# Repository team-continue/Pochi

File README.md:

# Pochi
CoREストライダー部門用のロボット「Pochi」のメインレポジトリです。

機体の構成は [Pochi の構成解説 — メカ・電装・制御](ROBOT_OVERVIEW.md) を参照してください。

詳細はドキュメントサイトを参照してください。

## 開発ルール
開発はブランチを切って Pull Request で main にマージしてください。main への直接コミットは禁止です。
ブランチ名: 機能追加は feature/hogehoge、バグ修正は fix/hogehoge
パッケージ名: pochi_hoge（タブ補完で一覧表示できるように）
Formatting (CI)
Push 時に CI が ament_clang_format を実行し、必要ならブランチへ自動コミットします。 main ブランチには自動 push しません。

## ビルド
``` shell
cd ~/ros2_ws
source /opt/ros/humble/setup.bash
rosdep install --from-paths src -i -y
colcon build --symlink-install
source install/setup.bash
```

## 起動方法
```
# シミュレータモード（デフォルト: /sim_odom使用）
ros2 launch core_launch navigation.launch.py

# シミュレータ + FAST-LIOオドメトリ
ros2 launch core_launch navigation.launch.py odom_source:=fastlio

# 実機モード（FAST-LIO + body_controller、TCP endpoint無し）
ros2 launch core_launch navigation.launch.py environment:=real

# 実機モード（GUI・ショートカットから）
# .bashrc が非対話シェルで早期 return するため、このラッパーを使用
ros2 run core_launch navigation.sh

# ボディコントローラ単体
ros2 launch core_launch navigation.launch.py environment:=real map_name:=curious_house.png

# 実機ハードウェア
ros2 launch core_hardware core_hardware.launch.py
```
Launch 引数の詳細はドキュメントサイトの「クイックスタート」を参照してください。

## 2026-10-14 の変更整理

作業版は `work/pochi-consolidation-20261014` に、CAD、起立・低速歩行、MPC・横ジャンプ、
LP-ACRLの過去実験、トルク余裕学習、歩行・停止の再学習を分けてコミットしています。
変更の記録は `pochi_rl/repository_state_20261014.json` を参照してください。

実際にSSH先で学習したソースとアセットは `archive/v19-ssh-20261014`、
Orinの実機コード・配布モデルは `archive/orin-hardware-20261014` に保存しています。
前者の作業ツリーは `.training-worktrees/v19-ssh-20261014/`、後者は
`.hardware-worktrees/orin-20261014/` です。SSH側の学習時のアセットと、この作業版の
CADアセットは異なるため、履歴を分けてそのまま残しています。

次の学習は利用許可が戻ったローカルGPUを使用します。大きい学習チェックポイント・
動画・CSVは各ホストの元の保存先に残し、実機起動に必要な小さいTorchScriptモデルと
契約は実機ブランチに含めています。機体固有のキャリブレーションはOrin上で保持します。
今回の整理は学習開始、実機の制御コード変更、サービス再起動を伴いません。

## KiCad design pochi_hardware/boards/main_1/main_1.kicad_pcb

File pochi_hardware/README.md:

# Pochi Hardware

Pochiの回路、STM32/Teensyファームウェア、ホスト側通信ツール、Python API、
Web joint viewerをまとめています。

## Python APIとWeb joint viewer

`pochi_client`はTeensy USB/UDP bridgeと通信するPython APIです。12台分のMIT指令を
1 packetで送信し、12台の状態とIMUを1 packetで受信します。Web viewerは左側の
3Dモデルへ現在姿勢を反映し、右側から関節の選択・目標角度・全体Torque ON/OFFを
操作できます。

### セットアップ

```bash
cd ~/Documents/GitHub/Pochi
uv sync

cd pochi_hardware/web
npm install
```

### Web joint viewer

3つのターミナルを使います。

#### 1. USB/UDP bridge

macOSではTeensyのdevice名を確認して起動します。

```bash
cd ~/Documents/GitHub/Pochi
uv run python pochi_hardware/src/teensy_udp_bridge.py \
  --serial /dev/cu.usbmodem176277501 \
  --command-bind 127.0.0.1:15000 \
  --state-dest 127.0.0.1:15001
```

#### 2. UDP/WebSocket server

```bash
cd ~/Documents/GitHub/Pochi
uv run python -m pochi_hardware.web.server
```

状態確認用URLは`http://127.0.0.1:8765/health`、WebSocketは
`ws://127.0.0.1:8765/ws`です。

#### 3. Web UI

```bash
cd ~/Documents/GitHub/Pochi/pochi_hardware/web
npm run dev
```

ブラウザで`http://127.0.0.1:3000`を開きます。

### Viewer controls and safety

- 左の3Dモデルは12軸の実角度を常時反映します。ドラッグで視点回転、スクロールでズーム、関節をクリックすると選択できます。
- 右の関節一覧または3Dモデルから1軸を選び、スライダーでMIT controlの目標角を更新します。
- `TORQUE ON`は全12台の現在角を初期目標に設定してから全軸をEnableします。
- 全12台から有効なCAN feedbackが返り、Faultがないときだけ`TORQUE ON`できます。
- 最後のWeb画面を閉じた場合、WebSocket serverは全軸を自動Disableします。
- WebSocket server終了時は全軸Disableとemergency-stop packetを送ります。
- Hip/Thigh/Calfの暫定UI制限はそれぞれ±55°、±150°、-165〜25°です。機構限界確定後にWeb UIとserverの両方を更新してください。

### Client API

```python
from pochi_client import PochiClient

with PochiClient() as robot:
    state = robot.wait_for_state(timeout=1.0)
    robot.set_mit(
        "front_left_hip",
        position_rad=0.2,
        velocity_rad_s=0.0,
        kp=20.0,
        kd=0.5,
        torque_nm=0.0,
        enable=True,
    )
    robot.disable_all()
```

### Joint layout

脚とCAN IDの対応です。各脚では足先側からIDが増えます。

| Leg | Hip | Thigh | Calf |
| --- | ---: | ---: | ---: |
| Front left | 2 | 1 | 0 |
| Rear left | 5 | 4 | 3 |
| Rear right | 8 | 7 | 6 |
| Front right | 11 | 10 | 9 |

Web画面には誤認防止のためCAN IDを常時表示します。

### テストとWebビルド

```bash
cd ~/Documents/GitHub/Pochi
uv run pytest -q

cd pochi_hardware/web
npm run build
```

## Jetson Orin NanoのSPI0ピン設定

`systemd/pochi-spi0-pinmux.service`は、Jetson Orin Nanoの40ピンヘッダーにある
SPI0をPochi用に設定します。

使用する物理ピンは次の4本です。

| 物理ピン | 信号 |
| --- | --- |
| 19 | SPI0 MOSI |
| 21 | SPI0 MISO |
| 23 | SPI0 SCK |
| 24 | SPI0 CS0 |

### インストールと有効化

以下は、この`pochi_hardware`ディレクトリで実行します。

```bash
sudo install -o root -g root -m 0644 \
  systemd/pochi-spi0-pinmux.service \
  /etc/systemd/system/pochi-spi0-pinmux.service

sudo systemctl daemon-reload
sudo systemctl enable --now pochi-spi0-pinmux.service
sudo systemctl restart pochi-spi0-pinmux.service
```

状態を確認します。

```bash
systemctl is-enabled pochi-spi0-pinmux.service
systemctl is-active pochi-spi0-pinmux.service
```

それぞれ`enabled`と`active`になれば設定完了です。

### STM32との通信確認

STM32へSPIエコーファームウェアを書き込んだ状態で、Orinから20 MHzのテストを
実行します。

```bash
cd ~/pochi
./orin_spi_test /dev/spidev0.0 20000000
```

成功時は次のように表示されます。

```text
TX=DE AD BE E1  ECHO=DE AD BE E1
PASS: STM32 echoed the Orin request
```

### 停止とGPIO設定の復元

サービスを停止すると`ExecStop`が実行され、SPIパッドを開発用Orinで取得した
元のGPIO設定へ戻します。

```bash
sudo systemctl disable --now pochi-spi0-pinmux.service
```

サービス自体も削除する場合は、停止後に次を実行します。

```bash
sudo rm -f /etc/systemd/system/pochi-spi0-pinmux.service
sudo systemctl daemon-reload
```

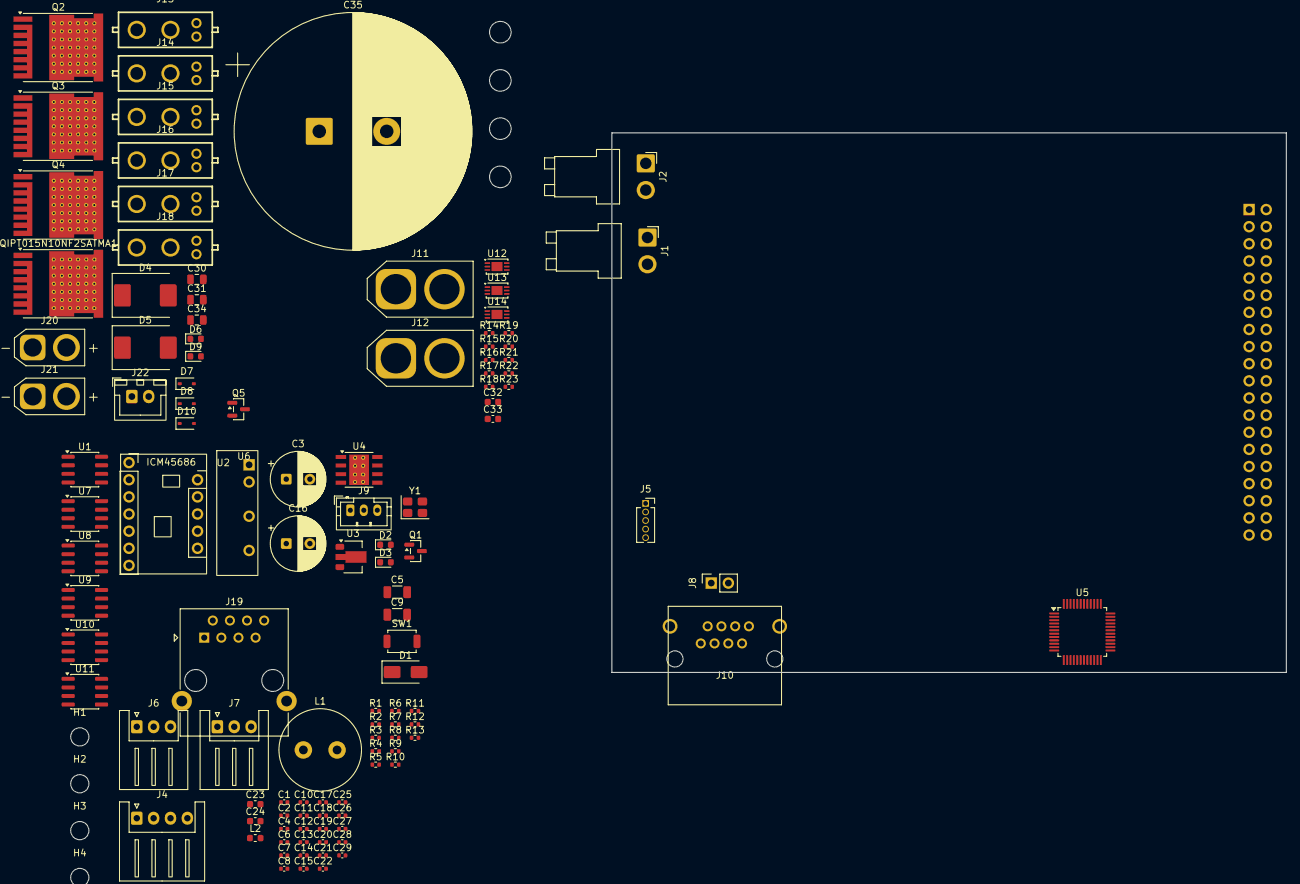
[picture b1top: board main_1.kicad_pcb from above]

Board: 2 copper layers, 100.0 x 80.0 mm, 122 parts (1 on the bottom side), 83 nets, no tracks yet.

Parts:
C1, C19, C20, C21, C22, C25, C26, C27, C28: 100n; C_0402_1005Metric
C2: 4.7u/16V; C_0402_1005Metric
C3, C16: 220u; CP_Radial_D8.0mm_P3.50mm
C4: 10u/0603/25V; C_0402_1005Metric
C5, C9: 4.7u; C_1206_3216Metric
C6, C7, C10, C13, C15: 100n/16V; C_0402_1005Metric
C8, C11: 10p/50V; C_0402_1005Metric
C12: 10u/0402/6.3V; C_0402_1005Metric
C14: 0.01u; C_0402_1005Metric
C17: 10n/50V; C_0402_1005Metric
C18: 1u/25V; C_0402_1005Metric
C23: 2.2u; C_0603_1608Metric
C24: 1u; C_0603_1608Metric
C29: 0.1u; C_0402_1005Metric
C30, C31, C34: 1.5u; C_0805_2012Metric
C32, C33: 10n; C_0603_1608Metric
C35: 10000u/50V; CP_Radial_D35.0mm_P10.00mm_SnapIn
D1: SS34; D_SMA
D2, D6: Green; LED_0603_1608Metric
D3: Yello; LED_0603_1608Metric
D4, D5: SMDJ48A; D_SMC
D7, D8, D10: IPT015N10NF2SATMA1; D_SOD-323
D9: RED; LED_0603_1608Metric
H1, H2, H3, H4: MountingHole; MountingHole_2.7mm_M2.5
H5, H6, H7, H8: MountingHole; MountingHole_3.2mm_M3_DIN965
J1, J2: VH; JST_VH_B2PS-VH_1x02_P3.96mm_Horizontal
J3: Conn_02x20_Odd_Even; PinSocket_2x20_P2.54mm_Vertical
J4: RS485; JST_XH_S4B-XH-A_1x04_P2.50mm_Horizontal
J5: Pad; PinSocket_1x05_P1.27mm_Vertical
J6, J7: XH; JST_XH_S3B-XH-A_1x03_P2.50mm_Horizontal
J8: DIP; PinSocket_1x02_P2.54mm_Vertical
J9: PH; JST_PH_B3B-PH-K_1x03_P2.00mm_Vertical
J10: RJ45; 7810-8P8C
J11, J12: XT60-M; AMASS_XT60-M_1x02_P7.20mm_Vertical
J13, J14, J15, J16, J17, J18: XT30(2+2)-M; CONN-TH_XT30PB-M
J19: RJ45; RJ45_Ninigi_GE
J20, J21: XT30; AMASS_XT30U-F_1x02_P5.0mm_Vertical
J22: XH; JST_XH_B2B-XH-A_1x02_P2.50mm_Vertical
L1: 22u; L_Radial_D12.0mm_P5.00mm_Fastron_11P
L2: 600Ω; L_0603_1608Metric
Q1: S9012; SOT-23
Q2, Q3, Q4: IPT015N10NF2SATMA1; Infineon_PG-HSOF-8-1_ThermalVias
Q5: 2N7002; SOT-23
QIPT015N10NF2SATMA1: NMOS; Infineon_PG-HSOF-8-1_ThermalVias
R1, R7, R8, R9: 120; R_0402_1005Metric
R2, R3, R18: 10k; R_0402_1005Metric
R4: 3.24k; R_0402_1005Metric
R5, R6: 47K; R_0402_1005Metric
R10: 7.5k; R_0402_1005Metric
R11: 20k; R_0402_1005Metric
R12, R13: 2.2k; R_0402_1005Metric
R14, R15: 47k; R_0402_1005Metric
R16, R17, R20: 1k; R_0402_1005Metric
R19: 10; R_0402_1005Metric
R21, R22: 15k; R_0402_1005Metric
R23: 4.7k; R_0402_1005Metric
SW1: RESET; SW_SPST_TS-1088-xR020
U1: SP3485EN; SOIC-8_3.9x4.9mm_P1.27mm
U2: ICM45686
U3: HT7533-1; SOT-89-3
U4: TPS5430DDA; TI_SO-PowerPAD-8_ThermalVias
U5: STM32G474CBTx; LQFP-48_7x7mm_P0.5mm
U6: MAU102
U7, U8, U9: ISO1044BD; SOIC-8_3.9x4.9mm_P1.27mm
U10: ADuM121N; SOIC-8_3.9x4.9mm_P1.27mm
U11: SP485E; SOIC-8_3.9x4.9mm_P1.27mm
U12, U13, U14: LTC4359-DCB; DFN-6-1EP_3x2mm_P0.5mm_EP1.65x1.35mm
Y1: 16MHz/9p; Crystal_SMD_3225-4Pin_3.2x2.5mm

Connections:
+3V3: C1.1, C2.1, C6.1, C10.1, C12.1, C13.1, C15.1, C19.1, C20.1, C21.1, C22.1, J5.2, L2.2, U1.8 (VCC), U2.2 (3V3), U3.3 (VO), U5.1 (VBAT), U5.20 (VREF+), U5.24 (VDD), U5.36 (VDD), U5.48 (VDD), U7.1 (VCC1), U8.1 (VCC1), U9.1 (VCC1), U10.1 (VDD1)
+5V: C4.1, C16.1, C23.1, J4.2, J6.2, J7.2, L1.2, R3.1, U3.2 (VI), U6.1 (+Vin)
+5VP: C24.1, C25.1, C26.1, C27.1, C28.1, C29.1, Q1.3 (C), R12.1, U6.6 (+Vout), U7.8 (VCC2), U8.8 (VCC2), U9.8 (VCC2), U10.8 (VDD2), U11.8 (VCC)
+48V: C30.1, J20.2, J21.2, Q2.1 (D), Q4.1 (D), R14.1, R21.1, U12.1 (OUT), U13.1 (OUT), U14.4 (IN)
/MCU/19V: C3.1, C5.1, C9.1, J1.2, J2.2, J8.1, R5.1, U4.7 (VIN)
/MCU/BOOT0: J3.27, R2.1, U5.45 (PB8)
/MCU/CAN1_H: J10.1, R7.1, U7.6 (CANH)
/MCU/CAN1_L: J10.2, R7.2, U7.5 (CANL)
/MCU/CAN1_RX: U5.33 (PA11), U7.3 (RXD)
/MCU/CAN1_TX: U5.46 (PB9), U7.2 (TXD)
/MCU/CAN2_H: J10.7, R8.1, U8.6 (CANH)
/MCU/CAN2_L: J10.8, R8.2, U8.5 (CANL)
/MCU/CAN2_RX: U5.42 (PB5), U8.3 (RXD)
/MCU/CAN2_TX: U5.43 (PB6), U8.2 (TXD)
/MCU/CAN3_H: J10.4, R9.1, U9.6 (CANH)
/MCU/CAN3_L: J10.5, R9.2, U9.5 (CANL)
/MCU/CAN3_RX: U5.40 (PB3), U9.3 (RXD)
/MCU/CAN3_TX: U5.41 (PB4), U9.2 (TXD)
/MCU/JTAG_RX: J3.8, U5.11 (PA3)
/MCU/JTAG_TX: J3.10, U5.10 (PA2)
/MCU/LED_MCU: R6.1, U5.18 (PB2)
/MCU/LED_PWM1: J6.3, U5.39 (PA15)
/MCU/LED_PWM2: J7.3, U5.9 (PA1)
/MCU/NRST: C7.2, J3.12, J3.29, J5.5, SW1.1, U5.7 (PG10)
/MCU/RS485_A: J4.3, R1.1, U1.6 (A)
/MCU/RS485_B: J4.4, R1.2, U1.7 (B)
/MCU/RS485_DE: U1.2 (~RE), U1.3 (DE), U5.34 (PA12)
/MCU/RS485_RX: U1.1 (RO), U5.32 (PA10)
/MCU/RS485_TX: U1.4 (DI), U5.31 (PA9)
/MCU/SPI_Master_INT: U2.10 (INT1), U5.30 (PA8)
/MCU/SPI_Master_MISO: U2.7 (MISO), U5.28 (PB14)
/MCU/SPI_Master_MOSI: U2.5 (MOSI), U5.29 (PB15)
/MCU/SPI_Master_NSS: U2.6 (CS), U5.26 (PB12)
/MCU/SPI_Master_SCK: U2.4 (SCK), U5.27 (PB13)
/MCU/SPI_Slave_MISO: J3.22, U5.14 (PA6)
/MCU/SPI_Slave_MOSI: J3.21, U5.15 (PA7)
/MCU/SPI_Slave_NSS: J3.24, U5.12 (PA4)
/MCU/SPI_Slave_SCK: J3.23, U5.13 (PA5)
/MCU/SWCLK: J5.3, U5.38 (PA14)
/MCU/SWDIO: J5.4, U5.37 (PA13)
/MCU/UART_RX_OUT: U10.7 (VIA), U11.1 (RO)
/MCU/UART_TTL: J9.3, U11.6 (A)
/MCU/UART_TX_OUT: R10.1, U10.6 (VOB), U11.4 (DI)
/Power/48V1: D4.1 (A1), D8.2 (A), J11.2, Q3.3 (S), U13.3 (SRC), U13.4 (IN)
/Power/48V2: D5.1 (A1), D7.2 (A), J12.2, Q2.3 (S), U12.3 (SRC), U12.4 (IN)
/Power/CAN1_H: J13.2, J14.2, J19.1
/Power/CAN1_L: J13.1, J14.1, J19.2
/Power/CAN2_H: J15.2, J16.2, J19.7
/Power/CAN2_L: J15.1, J16.1, J19.8
/Power/CAN3_H: J17.2, J18.2, J19.4
/Power/CAN3_L: J17.1, J18.1, J19.5
/Power/MotorPWR: C34.1, C35.1, J13.4, J14.4, J15.4, J16.4, J17.4, J18.4, QIPT015N10NF2SATMA1.1 (D), R15.1, U14.1 (OUT)
/Power/SHDN: C33.2, Q5.3 (D), U14.5 (~SHDN)
GND: C1.2, C2.2, C3.2, C4.2, C5.2, C6.2, C7.1, C8.2, C9.2, C10.2, C11.2, C12.2, C13.2, C15.2, C16.2, C17.2, C18.2, C19.2, C20.2, C21.2, C22.2, C23.2, D1.2 (A), D2.1 (K), D3.1 (K), J1.1, J2.1, J3.6, J3.9, J3.14, J3.20, J3.25, J3.30, J3.34, J3.39, J4.1, J5.1, J6.1, J7.1, J8.2, R2.2, R4.2, SW1.2, U1.5 (GND), U2.3 (GND), U3.1 (GND), U4.6 (GND), U4.9 (GNDPAD), U5.19 (VSSA), U5.23 (VSS), U5.35 (VSS), U5.47 (VSS), U6.2 (-Vin), U7.4 (GND1), U8.4 (GND1), U9.4 (GND1), U10.4 (GND1), Y1.2, Y1.4
GNDD: C24.2, C25.2, C26.2, C27.2, C28.2, C29.2, J9.1, J10.6, R11.2, R13.2, U6.4 (-Vout), U7.7 (GND2), U8.7 (GND2), U9.7 (GND2), U10.5 (GND2), U11.5 (GND)
GNDPWR: C32.1, C33.1, C35.2, D6.1 (K), D9.1 (K), J13.3, J14.3, J15.3, J16.3, J17.3, J18.3, J19.6, J20.1, J21.1, J22.1, Q5.2 (S), R16.2, R17.2, R20.2, R23.2
unnamed: C32.2, R18.1
unnamed: C14.2, D1.1 (K), L1.1, U4.8 (PH)
unnamed: D2.2 (A), R5.2
unnamed: D3.2 (A), R6.2
unnamed: D4.2 (A2), J11.1
unnamed: D5.2 (A2), J12.1
unnamed: D6.2 (A), R14.2
unnamed: D7.1 (K), Q2.2 (G), U12.2 (GATE)
unnamed: D8.1 (K), Q3.2 (G), U13.2 (GATE)
unnamed: D9.2 (A), R15.2
unnamed: D10.2 (A), Q4.3 (S), QIPT015N10NF2SATMA1.3 (S), U14.3 (SRC)
unnamed: D10.1 (K), QIPT015N10NF2SATMA1.2 (G), R18.2, R19.1, U14.2 (GATE)
unnamed: J22.2, Q5.1 (G), R22.2, R23.1
unnamed: Q1.1 (B), R10.2
unnamed: Q1.2 (E), R11.1, U11.2 (~RE), U11.3 (DE)
unnamed: C31.1, Q3.1 (D)
unnamed: Q4.2 (G), R19.2
unnamed: R21.2, R22.1
unnamed: C14.1, U4.1 (BOOT)
unnamed: R3.2, R4.1, U4.4 (VSENSE)
unnamed: C8.1, U5.5 (PF0), Y1.1
unnamed: C11.1, U5.6 (PF1), Y1.3
unnamed: C17.1, C18.1, L2.1, U5.21 (VDDA)
unnamed: R12.2, R13.1, U11.7 (B)
unnamed: C30.2, R16.1, U12.6 (Vss), U12.7 (Pad)
unnamed: C31.2, R17.1, U13.6 (Vss), U13.7 (Pad)
unnamed: C34.2, R20.1, U14.6 (Vss), U14.7 (Pad)

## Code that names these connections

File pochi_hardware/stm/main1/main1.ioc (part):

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Mcu.Name=STM32G474C(B-C-E)Tx
Mcu.Package=LQFP48
Mcu.UserName=STM32G474CBTx
PA1.GPIOParameters=GPIO_Label
PA1.GPIO_Label=LED_PWM2
PA1.Signal=S_TIM2_CH2
PA10.GPIOParameters=GPIO_Label
PA10.GPIO_Label=RS485_RX
PA10.Mode=Asynchronous
PA10.Signal=USART1_RX
PA11.Mode=FDCAN_Activate
PA11.Signal=FDCAN1_RX
PA12.GPIOParameters=GPIO_Label
PA12.GPIO_Label=RS485_DE
PA12.Mode=Hardware Flow Control (RS485)
PA12.Signal=USART1_DE
PA13.Mode=Serial_Wire
PA13.Signal=SYS_JTMS-SWDIO
PA14.Mode=Serial_Wire
PA14.Signal=SYS_JTCK-SWCLK
PA15.GPIOParameters=GPIO_Label
PA15.GPIO_Label=LED_PWM1
PA15.Signal=S_TIM2_CH1
PA2.GPIOParameters=GPIO_Label
PA2.GPIO_Label=JTAG_TX
PA2.Mode=Asynchronous
PA2.Signal=USART2_TX
PA3.GPIOParameters=GPIO_Label
PA3.GPIO_Label=JTAG_RX
PA3.Mode=Asynchronous
PA3.Signal=USART2_RX
PA4.GPIOParameters=GPIO_Label
PA4.GPIO_Label=SPI_Slave_NSS
PA4.Mode=NSS_Signal_Hard_Input
PA4.Signal=SPI1_NSS
PA5.GPIOParameters=GPIO_Label
PA5.GPIO_Label=SPI_Slave_SCK
PA5.Mode=Full_Duplex_Slave
PA5.Signal=SPI1_SCK
PA6.GPIOParameters=GPIO_Label
PA6.GPIO_Label=SPI_Slave_MISO
PA6.Mode=Full_Duplex_Slave
PA6.Signal=SPI1_MISO
PA7.GPIOParameters=GPIO_Label
PA7.GPIO_Label=SPI_Slave_MOSI
PA7.Mode=Full_Duplex_Slave
PA7.Signal=SPI1_MOSI
PA8.GPIOParameters=GPIO_Label
PA8.GPIO_Label=SPI_Master_INT
PA8.Signal=GPIO_Input
PA9.GPIOParameters=GPIO_Label
PA9.GPIO_Label=RS485_TX
PA9.Mode=Asynchronous
PA9.Signal=USART1_TX
PB10.GPIOParameters=GPIO_Label
PB10.GPIO_Label=TTL_TX
PB10.Mode=Asynchronous
PB10.Signal=USART3_TX
PB11.GPIOParameters=GPIO_Label
PB11.GPIO_Label=TTL_RX
PB11.Mode=Asynchronous
PB11.Signal=USART3_RX
PB12.GPIOParameters=GPIO_Label
PB12.GPIO_Label=SPI_Master_NSS
PB12.Mode=NSS_Signal_Hard_Output
PB12.Signal=SPI2_NSS
PB13.GPIOParameters=GPIO_Label
PB13.GPIO_Label=SPI_Master_SCK
PB13.Mode=Full_Duplex_Master
PB13.Signal=SPI2_SCK
PB14.GPIOParameters=GPIO_Label
PB14.GPIO_Label=SPI_Master_MISO
PB14.Mode=Full_Duplex_Master
PB14.Signal=SPI2_MISO
PB15.GPIOParameters=GPIO_Label
PB15.GPIO_Label=SPI_Master_MOSI
PB15.Mode=Full_Duplex_Master
PB15.Signal=SPI2_MOSI
PB2.GPIOParameters=GPIO_Label
PB2.GPIO_Label=LED_CPU
PB2.Signal=GPIO_Output
PB3.Mode=FDCAN_Activate
PB3.Signal=FDCAN3_RX
PB4.Mode=FDCAN_Activate
PB4.Signal=FDCAN3_TX
PB5.Mode=FDCAN_Activate
PB5.Signal=FDCAN2_RX
PB6.Mode=FDCAN_Activate
PB6.Signal=FDCAN2_TX
PB8-BOOT0.GPIOParameters=GPIO_Label
PB8-BOOT0.GPIO_Label=BOOT0
PB8-BOOT0.Signal=GPIO_Input
PB9.Mode=FDCAN_Activate
PB9.Signal=FDCAN1_TX
PF0-OSC_IN.Mode=HSE-External-Oscillator
PF0-OSC_IN.Signal=RCC_OSC_IN
PF1-OSC_OUT.Mode=HSE-External-Oscillator
PF1-OSC_OUT.Signal=RCC_OSC_OUT
RCC.HSE_VALUE=16000000
RCC.SYSCLKFreq_VALUE=170000000
RCC.SYSCLKSource=RCC_SYSCLKSOURCE_PLLCLK
board=custom

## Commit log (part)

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2026-05-09 Update package name from core_hoge to pochi_hoge
2026-05-09 add hardware branch
